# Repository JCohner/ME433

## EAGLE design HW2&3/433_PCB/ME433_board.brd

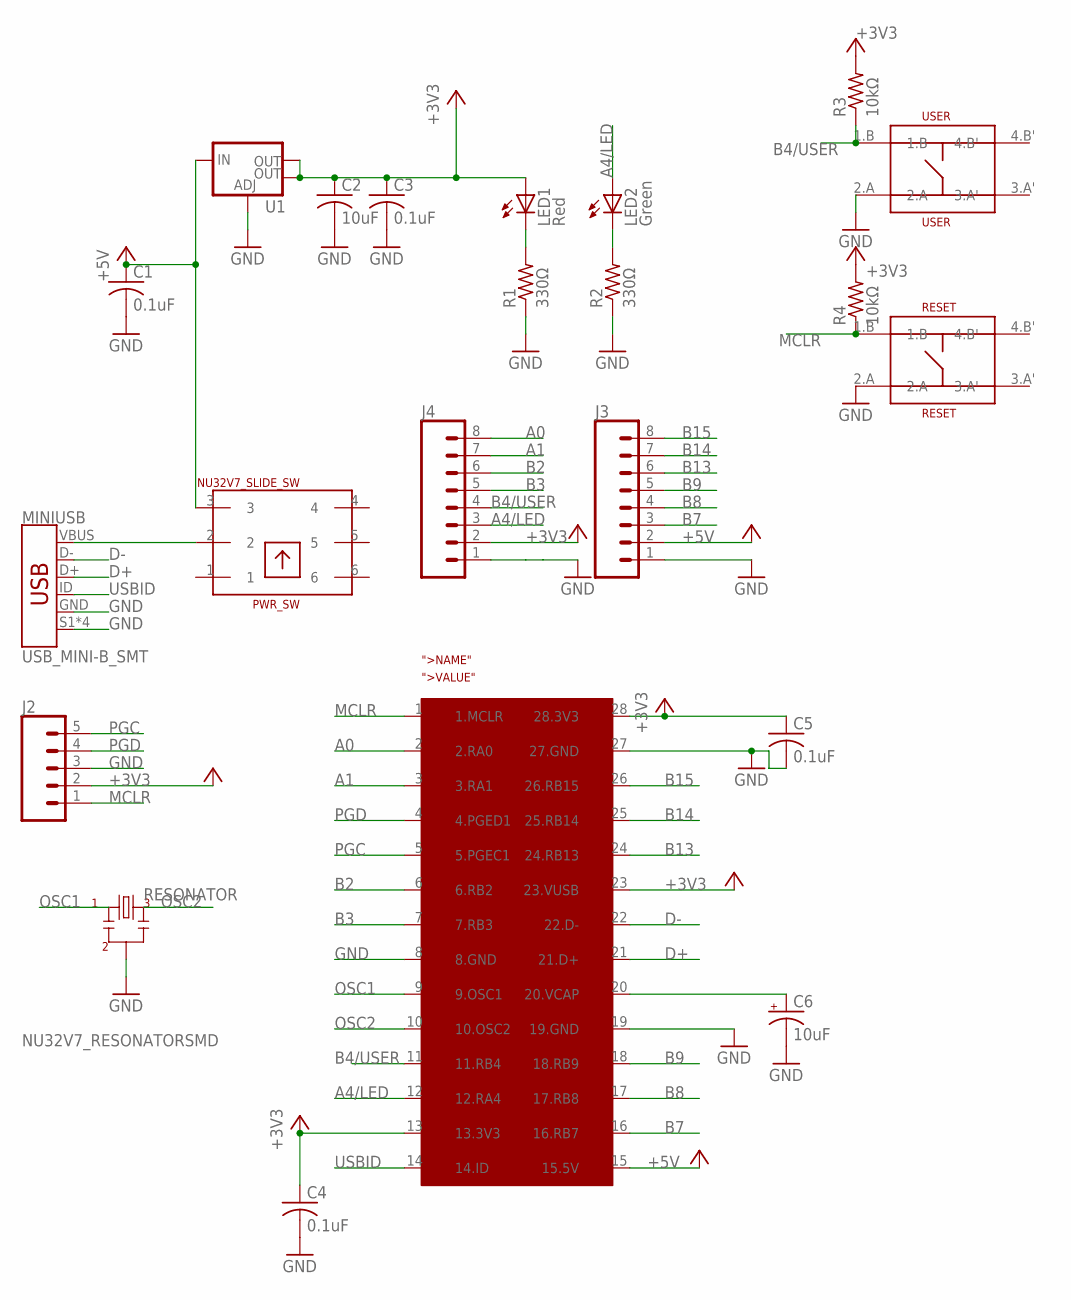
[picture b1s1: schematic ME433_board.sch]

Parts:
C1, C3, C4, C5: 0.1uF; C0603
C2: 10uF; C0603
C6: 10uF; 153CLV-0605
J2: CONN_05; 1X05
J3, J4: CONN_08"; 1X08
LED1: Red; SML0603
LED2: Green; SML0603
MINIUSB: USB_MINI-B_SMT; USB-MINIB
PWR_SW: NU32V7_SLIDE_SW
R1, R2: 330Ω; R0603
R3, R4: 10kΩ; R0603
RESET: RESET; NU32V7_MOM_SW
RESONATOR: NU32V7_RESONATORSMD; NU32V7_RESONATOR-SMD
U1: NU32V7_V_REG_LM1117SOT223; NU32V7_SOT223
U$1: PIC32; DIL28-3
USER: USER; NU32V7_MOM_SW

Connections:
+3V3: C2.1, C3.1, C4.1, C5.1, J2.2, J4.2, LED1.A, R3.2, R4.2, U1.2 (OUT), U1.4 (OUT), U$1.13 (13.3V3), U$1.23 (23.VUSB), U$1.28 (28.3V3)
+5V: C1.1, J3.2, PWR_SW.3, U1.3 (IN), U$1.15 (15.5V)
A0: J4.8, U$1.2 (2.RA0)
A1: J4.7, U$1.3 (3.RA1)
A4/LED: J4.3, LED2.A, U$1.12 (12.RA4)
B2: J4.6, U$1.6 (6.RB2)
B3: J4.5, U$1.7 (7.RB3)
B4/USER: J4.4, R3.1, U$1.11 (11.RB4), USER.1.B
B7: J3.3, U$1.16 (16.RB7)
B8: J3.4, U$1.17 (17.RB8)
B9: J3.5, U$1.18 (18.RB9)
B13: J3.6, U$1.24 (24.RB13)
B14: J3.7, U$1.25 (25.RB14)
B15: J3.8, U$1.26 (26.RB15)
D+: MINIUSB.D+, U$1.21 (21.D+)
D-: MINIUSB.D-, U$1.22 (22.D-)
GND: C1.2, C2.2, C3.2, C4.2, C5.2, C6.-, J2.3, J3.1, J4.1, MINIUSB.GND, MINIUSB.S1 (SHIELD), MINIUSB.S2 (SHIELD), MINIUSB.S3 (SHIELD), MINIUSB.S4 (SHIELD), R1.1, R2.1, RESET.2.A, RESONATOR.2, U1.1 (ADJ), U$1.8 (8.GND), U$1.19 (19.GND), U$1.27 (27.GND), USER.2.A
MCLR: J2.1, R4.1, RESET.1.B, U$1.1 (1.MCLR)
unnamed: MINIUSB.VBUS, PWR_SW.2
unnamed: LED2.C, R2.2
unnamed: LED1.C, R1.2
unnamed: C6.+, U$1.20 (20.VCAP)
OSC1: RESONATOR.1, U$1.9 (9.OSC1)
OSC2: RESONATOR.3, U$1.10 (10.OSC2)
PGC: J2.5, U$1.5 (5.PGEC1)
PGD: J2.4, U$1.4 (4.PGED1)
USBID: MINIUSB.ID, U$1.14 (14.ID)

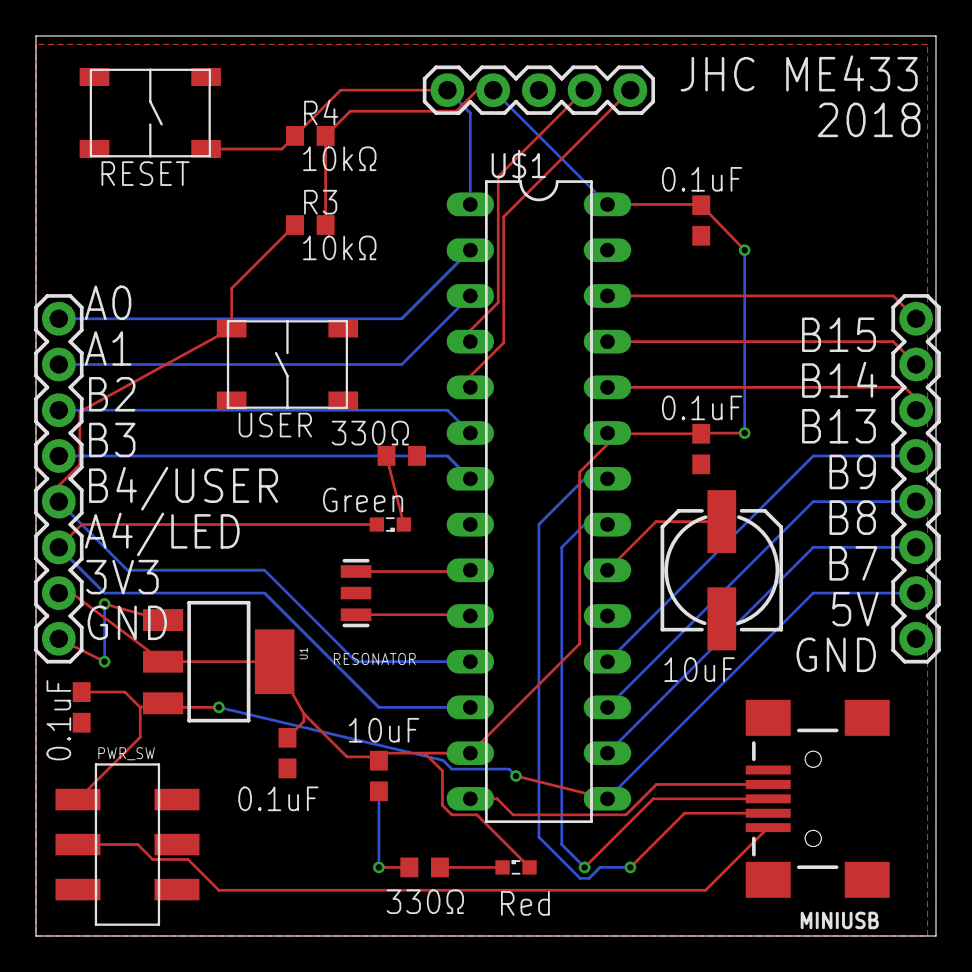
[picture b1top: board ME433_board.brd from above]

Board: 2 copper layers, 50.0 x 50.0 mm, 22 parts (0 on the bottom side), 27 nets.

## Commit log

2018-04-07 part 2
2018-04-07 part3
2018-04-08 part4_code
2018-04-08 blinky_helloworld
2018-04-08 USR led working
2018-04-08 finished
2018-04-08 demo_video
2018-04-16 redid hw2 with smd components
2018-04-16 board design and gerber generation
2018-04-16 hw2->hw2&3
2018-05-04 hw5-almost
2018-05-06 hw5_functional
2018-05-06 complete_demo
2018-05-08 editor config updates
2018-05-29 working hw7
2018-05-31 HW8 readme
2018-05-31 HW8_Fix
2018-05-31 wonky_check
2018-06-01 wonky
2018-06-01 HW10
2018-06-09 HW10 update, HW12 final
2018-06-09 CAD + Camera
2018-06-12 Android Work
2018-06-12 hw14 complete
2018-06-12 motor_driving code + working hw13 (finally)
2018-06-13 PI Control
2018-06-13 HW17 setup
2018-06-13 HW17 complete
2018-06-19 HW18

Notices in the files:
parts and their libraries:
SparkFun-Connectors: Licensing: Creative Commons ShareAlike 4.0 International - https://creativecommons.org/licenses/by-sa/4.0
